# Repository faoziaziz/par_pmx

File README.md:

# par_pmx

berisi design hardware dan gateway untuk akses ke zabbix

hardware ada dalam direktory ***pg_hw*** gateway ada dalam direktory ***gateway***

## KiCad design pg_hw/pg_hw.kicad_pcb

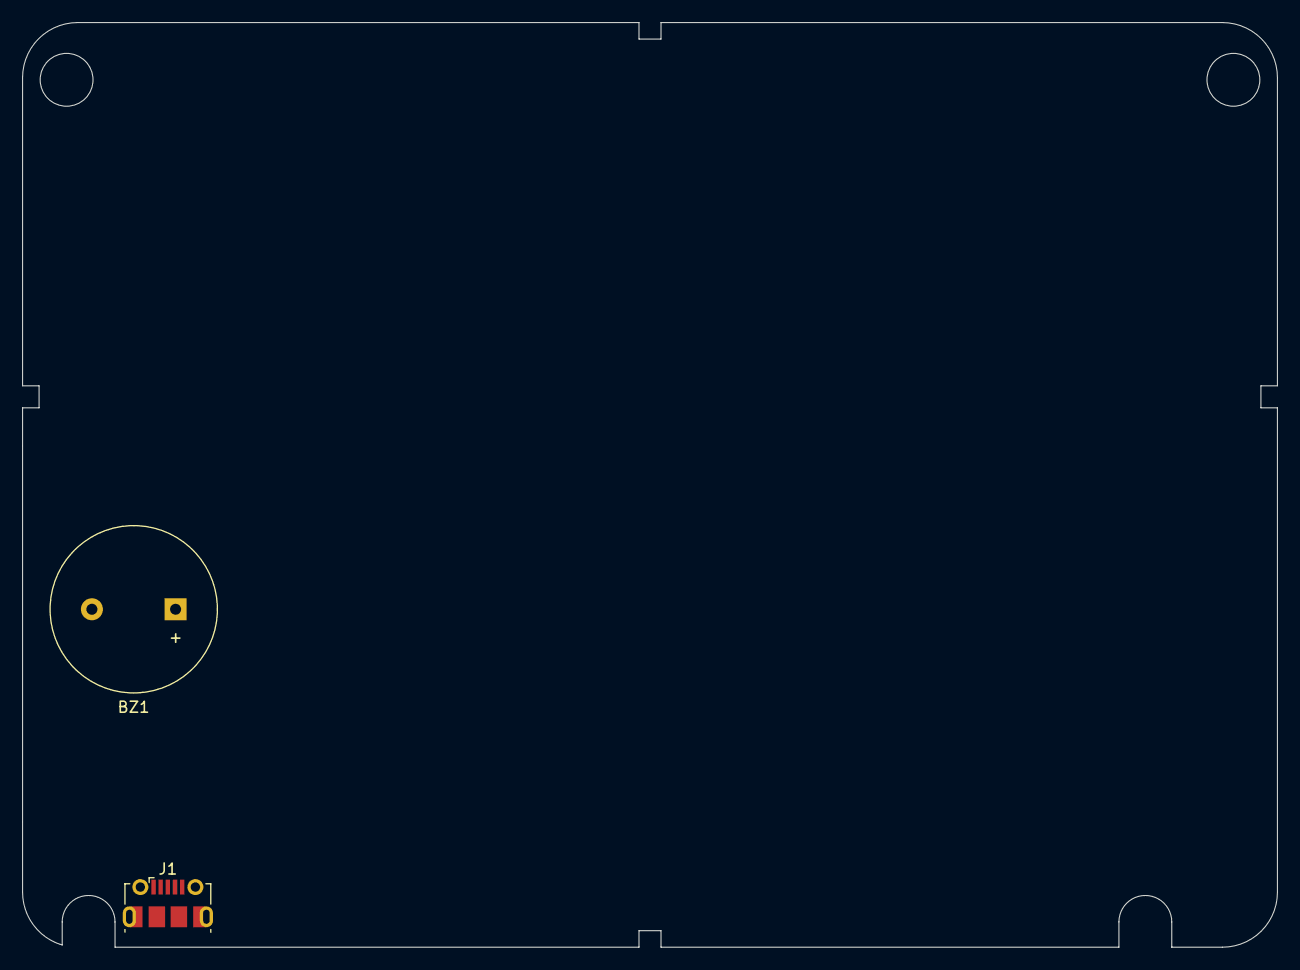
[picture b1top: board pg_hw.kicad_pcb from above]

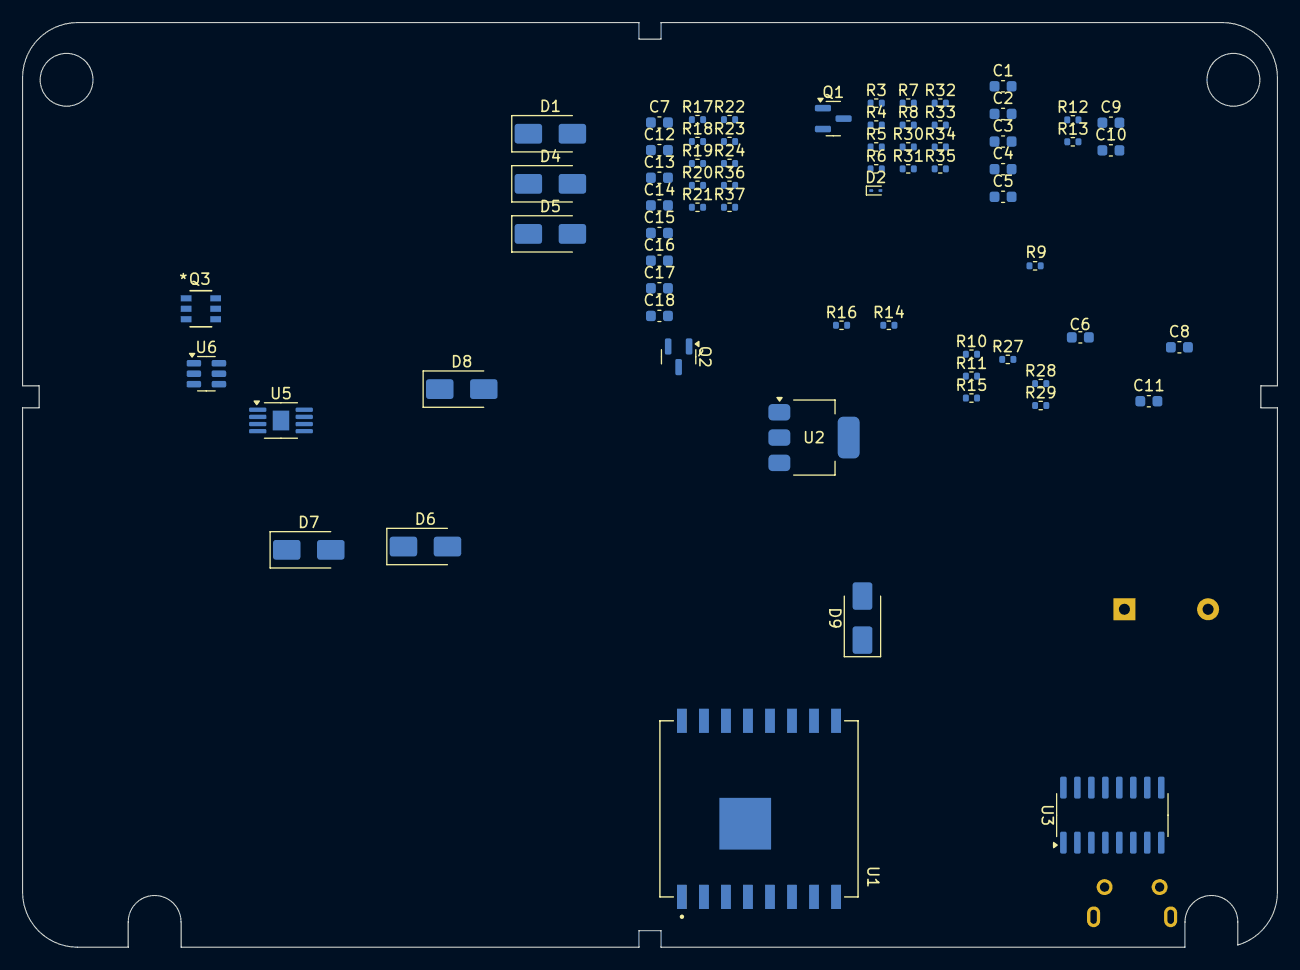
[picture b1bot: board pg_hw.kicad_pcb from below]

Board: 2 copper layers, 114.0 x 84.0 mm, 69 parts (67 on the bottom side), 37 nets, no tracks yet.

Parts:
BZ1: Buzzer; Buzzer_15x7.5RM7.6
C1, C4: 0.1uF; C_0603_1608Metric
C2, C3, C6: 10uF; C_0603_1608Metric
C5, C10: 1uF; C_0603_1608Metric
C7, C12, C13, C14, C15, C16, C17, C18: C; C_0603_1608Metric
C8: 100nF; C_0603_1608Metric
C9: 0.47uF; C_0603_1608Metric
C11: 10uC; C_0603_1608Metric
D1, D4, D5, D6, D7, D8, D9: SS14; D_SMA
D2: ESD9B5.0ST5G; D_SOD-923
J1: USB_B_Micro; USB_Micro-B_Molex-105017-0001
Q1, Q2: SS8050; SOT-23
Q3: FS8205A; SOT-23-6L_TCP
R3, R5: 12K; R_0402_1005Metric
R4, R6, R7, R8, R12, R13, R35: 10K; R_0402_1005Metric
R9: 1; R_0402_1005Metric
R10, R15, R27, R28, R29: 1K; R_0402_1005Metric
R11: 1.5K; R_0402_1005Metric
R14: 0.01; R_0402_1005Metric
R16: 100; R_0402_1005Metric
R17, R18, R19, R20, R21, R22, R23, R24: R; R_0402_1005Metric
R30, R31, R32, R33, R34, R37: 0; R_0402_1005Metric
R36: 1k; R_0402_1005Metric
U1: BW16; MODULE_BW16
U2: AMS1117-3.3; SOT-223-3_TabPin2
U3: CH340C; SOP-16_3.9x9.9mm_P1.27mm
U5: TP4056; MSOP-8-1EP_3x3mm_P0.65mm_EP1.5x1.8mm
U6: DW01A; SOT-23-6

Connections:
4.2V: C1.1, C2.1, C9.1, C9.2, C10.1, C10.2, C11.1, R13.2, R14.1, R14.2, R16.1, U2.3 (VI), U5.5 (BAT)
+3V3: BZ1.1 (+), C3.1, C4.1, C12.1, C14.1, C16.1, C18.1, R4.1, R6.2, R7.1, R8.1, R12.1, R17.2, R18.2, R19.2, R20.2, R21.2, R22.2, R23.2, R24.2, R27.1, R35.1, R36.1, R37.1, U1.8 (VDD_3V3), U2.2 (VO), U3.4 (V3), U3.16 (VCC)
+5V: D4.1 (K), R9.1, R10.1, U5.4 (VCC), U5.8 (CE)
/Controller/CH340_RX0: R32.1, R33.2
/Controller/CH340_TXD: D9.1 (K), U3.2 (TXD)
/Controller/CHIP_EN: C5.1, Q1.3 (C), U1.3 (CHIP_EN)
/Controller/DTR: Q2.2 (E), R3.1, U3.13 (~DTR)
/Controller/PA7_TX: Q2.3 (C), R33.1, R34.1
/Controller/PA8_LOG_RX: D1.1 (K), D8.1 (K)
/Controller/PA8_RX: D1.2 (A), D8.2 (A), R4.2, R31.2
/Controller/PA27: R35.2, U1.6 (PA27)
/Controller/PB1_TXD: R32.2, U1.16 (PB1)
/Controller/PB2_RXD: D5.2 (A), R6.1, R30.1, U1.15 (PB2)
/Controller/RTS: Q1.2 (E), R5.1, U3.14 (~RTS)
/Controller/VBUS: D2.1 (A1), D4.2 (A), J1.1 (VBUS)
/Controller/usb_d+: J1.3 (D+), U3.5 (UD+)
/Controller/usb_d-: J1.2 (D-), U3.6 (UD-)
BAT-: C8.2, Q3.3, U6.6 (GND)
BUZZER: R29.2, R34.2
CTP_SCL: R7.2, U1.10 (PA25)
CTP_SDA: R8.2, U1.7 (PA26)
unnamed: BZ1.2 (-), R27.2
unnamed: C6.1, R9.2
unnamed: D6.2 (A), D7.2 (A), R10.2
unnamed: D6.1 (K), U5.6 (*STDBY)
unnamed: D7.1 (K), U5.7 (*CHRG)
unnamed: D9.2 (A), R30.2, R31.1
unnamed: R36.2, R37.2
unnamed: Q1.1 (B), R3.2
unnamed: Q2.1 (B), R5.2
unnamed: R28.1, R29.1
unnamed: R11.1, U5.2 (PROG)
unnamed: R15.2, U6.2 (CS)
unnamed: Q3.6, U6.3 (OC)
unnamed: Q3.4, U6.1 (OD)
unnamed: C8.1, R16.2, U6.5 (VCC)
OUT-: C1.2, C2.2, C3.2, C4.2, C5.2, C6.2, C7.2, C11.2, C12.2, C13.2, C14.2, C15.2, C16.2, C17.2, C18.2, D2.2 (A2), J1.5 (GND), J1.6 (Shield), Q3.1, R11.2, R15.1, R28.2, U1.9 (GND), U2.1 (GND), U3.1 (GND), U5.1 (TEMP), U5.3 (GND)

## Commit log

2024-12-18 add hardware design and gateway
2024-12-18 add hardware
2024-12-22 Add some libarry
    ad some library
2024-12-23 updarte schematics
    schematics menuju pengecheckan
2025-01-02 update some things
2025-01-02 add one batt
    add one bat
2025-01-06 change batt again
2025-01-11 push
2025-01-13 ADD REV
    DADA
2025-01-13 ada
    dada
2025-01-13 Mungkin masih akan ada refisi
    munvkin
2025-01-13 charlotte andeh
    charlotte andeh
2025-01-13 addd draw
2025-01-14 update ke lcd
    lcd diupdate
2025-01-14 usb revision
    add some revision
2025-01-14 adad
    dada
2025-01-14 update ttp
2025-01-14 update touch pad
2025-02-20 add some
    add some
2025-02-20 comit
    commit end
2025-02-20 comit
    commit endsa
2025-02-24 ahzeq
    ahzeq
